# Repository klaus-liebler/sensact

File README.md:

# sensact

Verteilte Hausautomatisierung – Hardware, Firmware, Werkzeuge und Weboberfläche.

Stationen an einem gemeinsamen CAN-Bus lesen Taster und Drehgeber und schalten Licht, Rollläden, Pumpen
und Signale. Die kleinste Einheit ist die **App** (Taster, Lampe, Rollladen …) mit einer hausweit
eindeutigen Nummer; Apps schicken einander Kommandos, egal auf welcher Station sie laufen. Was wo
verdrahtet ist, beschreibt ein **XML-Hausmodell**, aus dem Konfiguration und Weboberfläche jeder Station
erzeugt werden.

**Dokumentation: [docs/README.md](docs/README.md)** – Fachkonzepte, Bedienung im Haus,
Weboberfläche, Betrieb und Änderungen.

## Inhalt des Repos

| Ordner | Inhalt |
|---|---|
| [`docs/`](docs/README.md) | Fachkonzepte und Nutzerdokumentation |
| [`firmware/sensact_firmware/`](firmware/sensact_firmware/README.md) | ESP32-S3-Basis-Firmware, Builder, Editor, Hausmodell (`model/`), Weboberfläche – mit Entwicklerdokumentation |
| [`firmware/sensact_firmware_f103/`](firmware/sensact_firmware_f103/README.md) | Firmware der sensactUp-Stationen (STM32F103) auf rtoos |
| [`espidf-components/sensact-applicationmodel/`](espidf-components/sensact-applicationmodel/README.md) | die Apps (gemeinsam für ESP32 und STM32F103) mit Host-Tests |
| `espidf-components/sensact-middleware/`, `sensact-hal/`, `sensactcommon/` | CAN-Codec, HAL-Basis, gemeinsame Typen |
| `firmware/sensact_firmware_stm32/`, `firmware/firmwareCubeIDE/` | Altfirmware der STM32F407-Station |
| `pcb/` | Platinen (KiCad) |
| `doc/` | Datenblätter |
| `runware/` | PC-Werkzeuge (UDP-Monitor) |

## Hardware

- **SensactHS** – Hutschienenmontage im Verteiler (Technikstationen mit I2C-Erweiterungen für Ein- und Ausgänge)
- **SensactUP** – Unterputzmontage im Raum (Taster, Drehgeber, Signal-LEDs)
- Spezialstationen für Fingerabdruckleser (Seitentür) und Außenbereich (Terrasse)

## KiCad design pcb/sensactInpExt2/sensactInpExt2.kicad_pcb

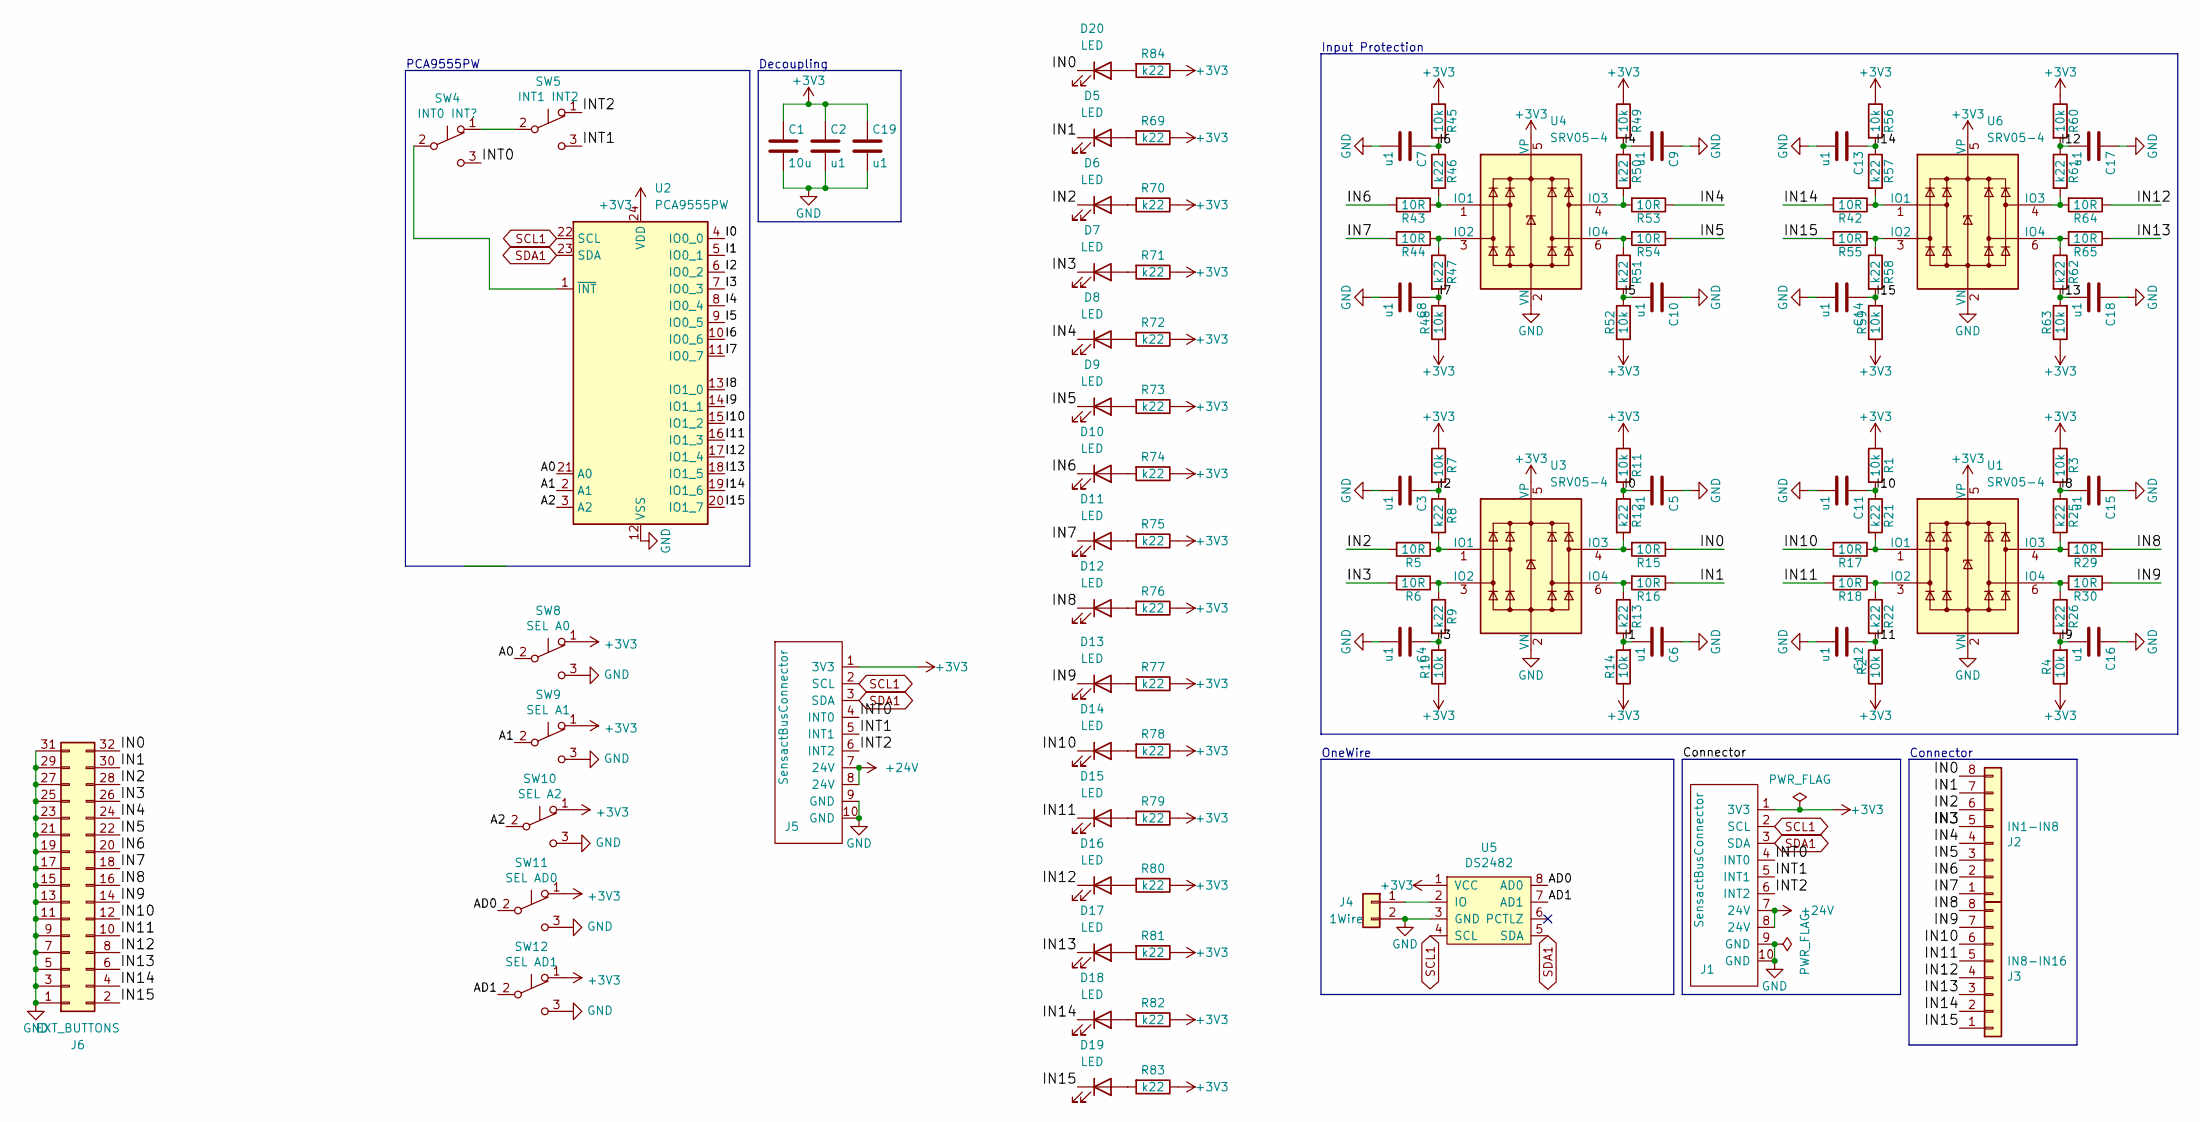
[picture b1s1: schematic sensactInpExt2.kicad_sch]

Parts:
C1: 10u; C_0805_2012Metric
C2, C3, C4, C5, C6, C7, C8, C9, C10, C11, C12, C13, C14, C15, C16, C17, C18, C19: u1; C_0402_1005Metric
D5, D6, D7, D8, D9, D10, D11, D12, D13, D14, D15, D16, D17, D18, D19, D20: LED; LED_1606
J1: SensactBusConnector; IDC-Header_2x05_P2.54mm_Horizontal
J2: IN1-IN8; PhoenixContact_MC_0,5_8-G-2.5_1x08_P2.50mm_Horizontal
J3: IN8-IN16; PhoenixContact_MC_0,5_8-G-2.5_1x08_P2.50mm_Horizontal
J4: 1Wire; PhoenixContact_MC_1,5_2-G-3.81_1x02_P3.81mm_Horizontal
J5: SensactBusConnector; PinSocket_2x06_P2.54mm_Vertical
J6: EXT_BUTTONS; PinHeader_2x16_P2.54mm_Horizontal
R1, R2, R3, R4, R7, R10, R11, R14, R45, R48, R49, R52, R56, R59, R60, R63: 10k; R_0402_1005Metric
R5, R6, R15, R16, R17, R18, R29, R30, R42, R43, R44, R53, R54, R55, R64, R65: 10R; R_0402_1005Metric
R8, R9, R12, R13, R21, R22, R25, R26, R46, R47, R50, R51, R57, R58, R61, R62, R69, R70, R71, R72, R73, R74, R75, R76, R77, R78, R79, R80, R81, R82, R83, R84: k22; R_0402_1005Metric
SW4: INT0 INT?; SW_SPDT_PCM12
SW5: INT1 INT2; SW_SPDT_PCM12
SW8: SEL A0; SW_SPDT_PCM12
SW9: SEL A1; SW_SPDT_PCM12
SW10: SEL A2; SW_SPDT_PCM12
SW11: SEL AD0; SW_SPDT_PCM12
SW12: SEL AD1; SW_SPDT_PCM12
U1, U3, U4, U6: SRV05-4; SOT-23-6
U2: PCA9555PW; TSSOP-24_4.4x7.8mm_P0.65mm
U5: DS2482; SOIC-8_3.9x4.9mm_P1.27mm

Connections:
+3V3: C1.1, C2.1, C19.1, J1.1 (3V3), J5.1 (3V3), R1.1, R2.1, R3.1, R4.1, R7.1, R10.1, R11.1, R14.1, R45.1, R48.1, R49.1, R52.1, R56.1, R59.1, R60.1, R63.1, R69.1, R70.1, R71.1, R72.1, R73.1, R74.1, R75.1, R76.1, R77.1, R78.1, R79.1, R80.1, R81.1, R82.1, R83.1, R84.1, SW8.1 (A), SW9.1 (A), SW10.1 (A), SW11.1 (A), SW12.1 (A), U1.5 (VP), U2.24 (VDD), U3.5 (VP), U4.5 (VP), U5.1 (VCC), U6.5 (VP)
+24V: J1.7 (24V), J1.8 (24V), J5.7 (24V), J5.8 (24V)
/A0: SW8.2 (B), U2.21 (A0)
/A1: SW9.2 (B), U2.2 (A1)
/A2: SW10.2 (B), U2.3 (A2)
/AD0: SW11.2 (B), U5.8 (AD0)
/AD1: SW12.2 (B), U5.7 (AD1)
/I0: C5.2, R11.2, R12.1, U2.4 (IO0_0)
/I1: C6.2, R13.2, R14.2, U2.5 (IO0_1)
/I2: C3.1, R7.2, R8.1, U2.6 (IO0_2)
/I3: C4.1, R9.2, R10.2, U2.7 (IO0_3)
/I4: C9.2, R49.2, R50.1, U2.8 (IO0_4)
/I5: C10.2, R51.2, R52.2, U2.9 (IO0_5)
/I6: C7.1, R45.2, R46.1, U2.10 (IO0_6)
/I7: C8.1, R47.2, R48.2, U2.11 (IO0_7)
/I8: C15.2, R3.2, R25.1, U2.13 (IO1_0)
/I9: C16.2, R4.2, R26.2, U2.14 (IO1_1)
/I10: C11.1, R1.2, R21.1, U2.15 (IO1_2)
/I11: C12.1, R2.2, R22.2, U2.16 (IO1_3)
/I12: C17.2, R60.2, R61.1, U2.17 (IO1_4)
/I13: C18.2, R62.2, R63.2, U2.18 (IO1_5)
/I14: C13.1, R56.2, R57.1, U2.19 (IO1_6)
/I15: C14.1, R58.2, R59.2, U2.20 (IO1_7)
/IN0: D20.1 (K), J2.8, J6.32, R15.1
/IN1: D5.1 (K), J2.7, J6.30, R16.1
/IN2: D6.1 (K), J2.6, J6.28, R5.2
/IN3: D7.1 (K), J2.5, J6.26, R6.2
/IN4: D8.1 (K), J2.4, J6.24, R53.1
/IN5: D9.1 (K), J2.3, J6.22, R54.1
/IN6: D10.1 (K), J2.2, J6.20, R43.2
/IN7: D11.1 (K), J2.1, J6.18, R44.2
/IN8: D12.1 (K), J3.8, J6.16, R29.1
/IN9: D13.1 (K), J3.7, J6.14, R30.1
/IN10: D14.1 (K), J3.6, J6.12, R17.2
/IN11: D15.1 (K), J3.5, J6.10, R18.2
/IN12: D16.1 (K), J3.4, J6.8, R64.1
/IN13: D17.1 (K), J3.3, J6.6, R65.1
/IN14: D18.1 (K), J3.2, J6.4, R42.2
/IN15: D19.1 (K), J3.1, J6.2, R55.2
/INT0: J1.4 (INT0), J5.4 (INT0), SW4.3 (C)
/INT1: J1.5 (INT1), J5.5 (INT1), SW5.3 (C)
/INT2: J1.6 (INT2), J5.6 (INT2), SW5.1 (A)
GND: C1.2, C2.2, C3.2, C4.2, C5.1, C6.1, C7.2, C8.2, C9.1, C10.1, C11.2, C12.2, C13.2, C14.2, C15.1, C16.1, C17.1, C18.1, C19.2, J1.9 (GND), J1.10 (GND), J4.2, J5.9 (GND), J5.10 (GND), J6.1, J6.3, J6.5, J6.7, J6.9, J6.11, J6.13, J6.15, J6.17, J6.19, J6.21, J6.23, J6.25, J6.27, J6.29, J6.31, SW8.3 (C), SW9.3 (C), SW10.3 (C), SW11.3 (C), SW12.3 (C), U1.2 (VN), U2.12 (VSS), U3.2 (VN), U4.2 (VN), U5.3 (GND), U6.2 (VN)
unnamed: D5.2 (A), R69.2
unnamed: D6.2 (A), R70.2
unnamed: D7.2 (A), R71.2
unnamed: D8.2 (A), R72.2
unnamed: D9.2 (A), R73.2
unnamed: D10.2 (A), R74.2
unnamed: D11.2 (A), R75.2
unnamed: D12.2 (A), R76.2
unnamed: D13.2 (A), R77.2
unnamed: D14.2 (A), R78.2
unnamed: D15.2 (A), R79.2
unnamed: D16.2 (A), R80.2
unnamed: D17.2 (A), R81.2
unnamed: D18.2 (A), R82.2
unnamed: D19.2 (A), R83.2
unnamed: D20.2 (A), R84.2
unnamed: J4.1, U5.2 (IO)
unnamed: SW4.1 (A), SW5.2 (B)
unnamed: SW4.2 (B), U2.1 (~INT)
unnamed: R17.1, R21.2, U1.1 (IO1)
unnamed: R18.1, R22.1, U1.3 (IO2)
unnamed: R25.2, R29.2, U1.4 (IO3)
unnamed: R26.1, R30.2, U1.6 (IO4)
unnamed: R5.1, R8.2, U3.1 (IO1)
unnamed: R6.1, R9.1, U3.3 (IO2)
unnamed: R12.2, R15.2, U3.4 (IO3)
unnamed: R13.1, R16.2, U3.6 (IO4)
unnamed: R43.1, R46.2, U4.1 (IO1)
unnamed: R44.1, R47.1, U4.3 (IO2)
unnamed: R50.2, R53.2, U4.4 (IO3)
unnamed: R51.1, R54.2, U4.6 (IO4)
unnamed: R42.1, R57.2, U6.1 (IO1)
unnamed: R55.1, R58.1, U6.3 (IO2)
unnamed: R61.2, R64.2, U6.4 (IO3)
unnamed: R62.1, R65.2, U6.6 (IO4)
SCL1: J1.2 (SCL), J5.2 (SCL), U2.22 (SCL), U5.4 (SCL)
SDA1: J1.3 (SDA), J5.3 (SDA), U2.23 (SDA), U5.5 (SDA)

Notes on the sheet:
OneWire
Decoupling
Input Protection
Connector
PCA9555PW

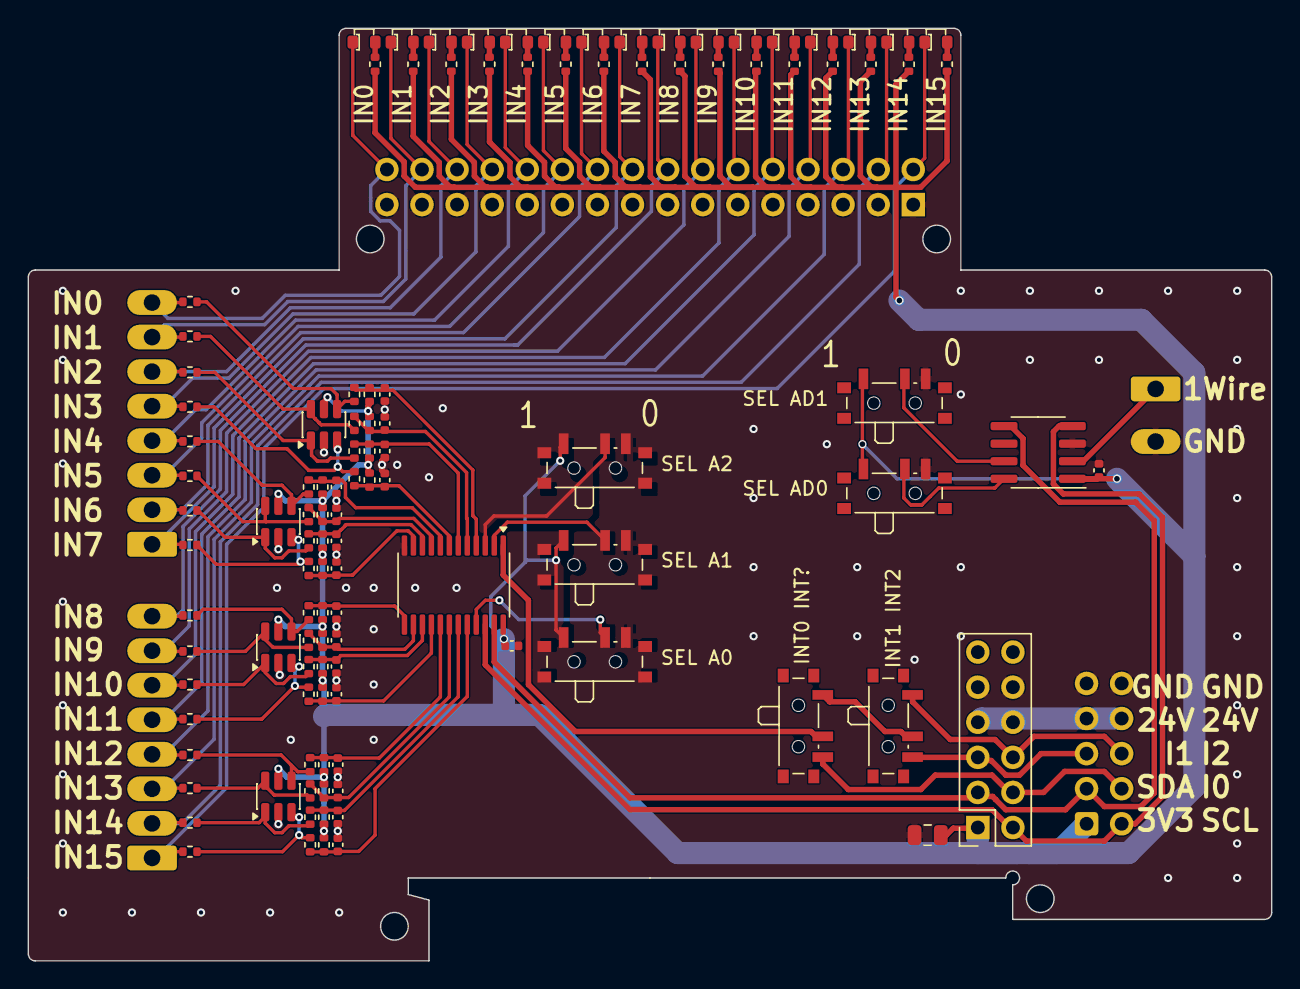
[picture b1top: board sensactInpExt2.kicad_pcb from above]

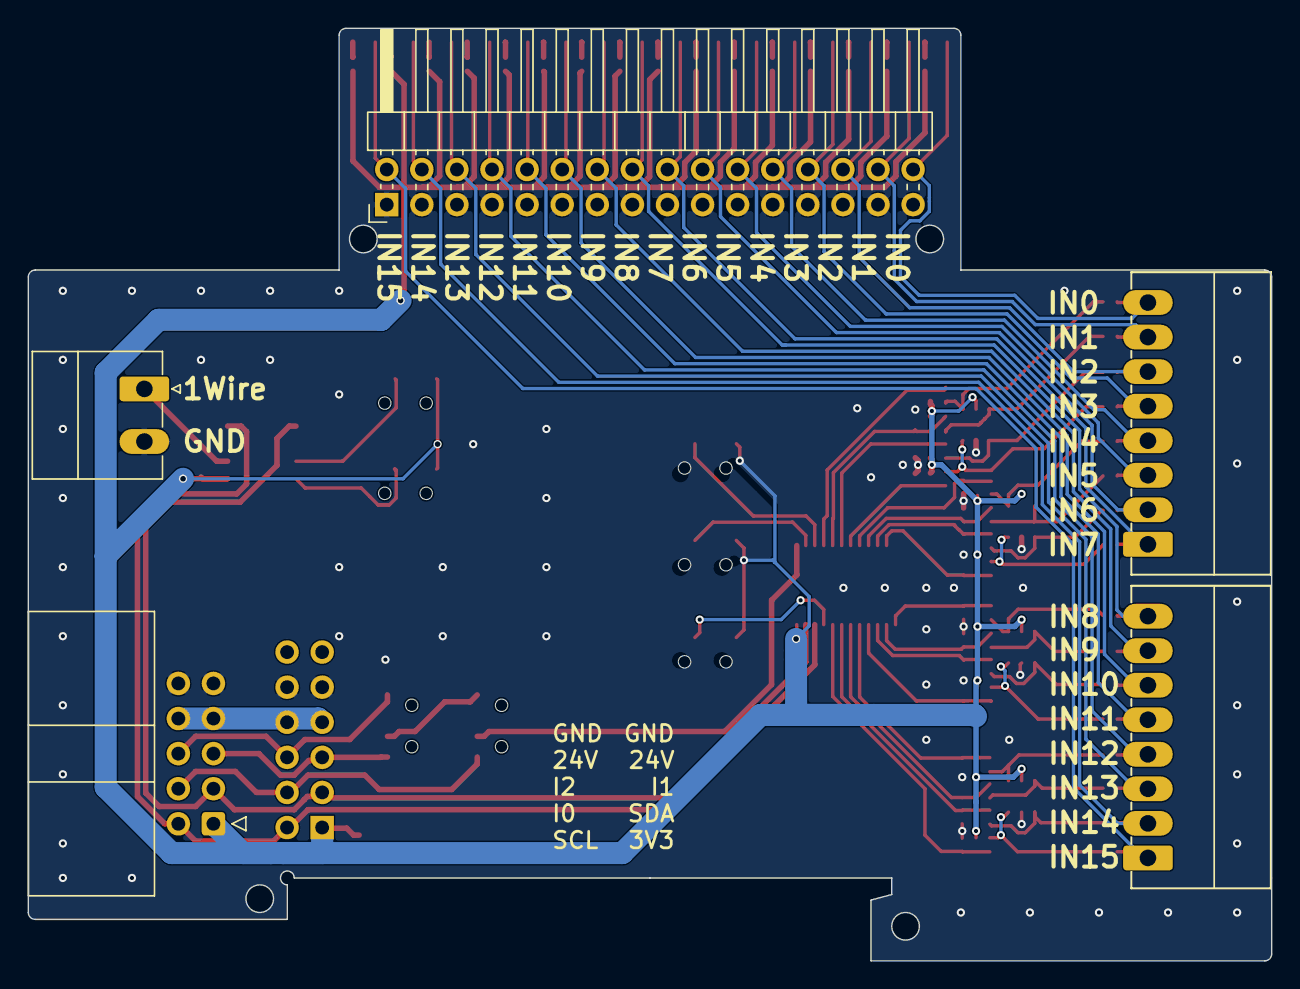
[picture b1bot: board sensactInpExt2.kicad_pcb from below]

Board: 2 copper layers, 90.0 x 67.5 mm, 118 parts (5 on the bottom side), 80 nets.

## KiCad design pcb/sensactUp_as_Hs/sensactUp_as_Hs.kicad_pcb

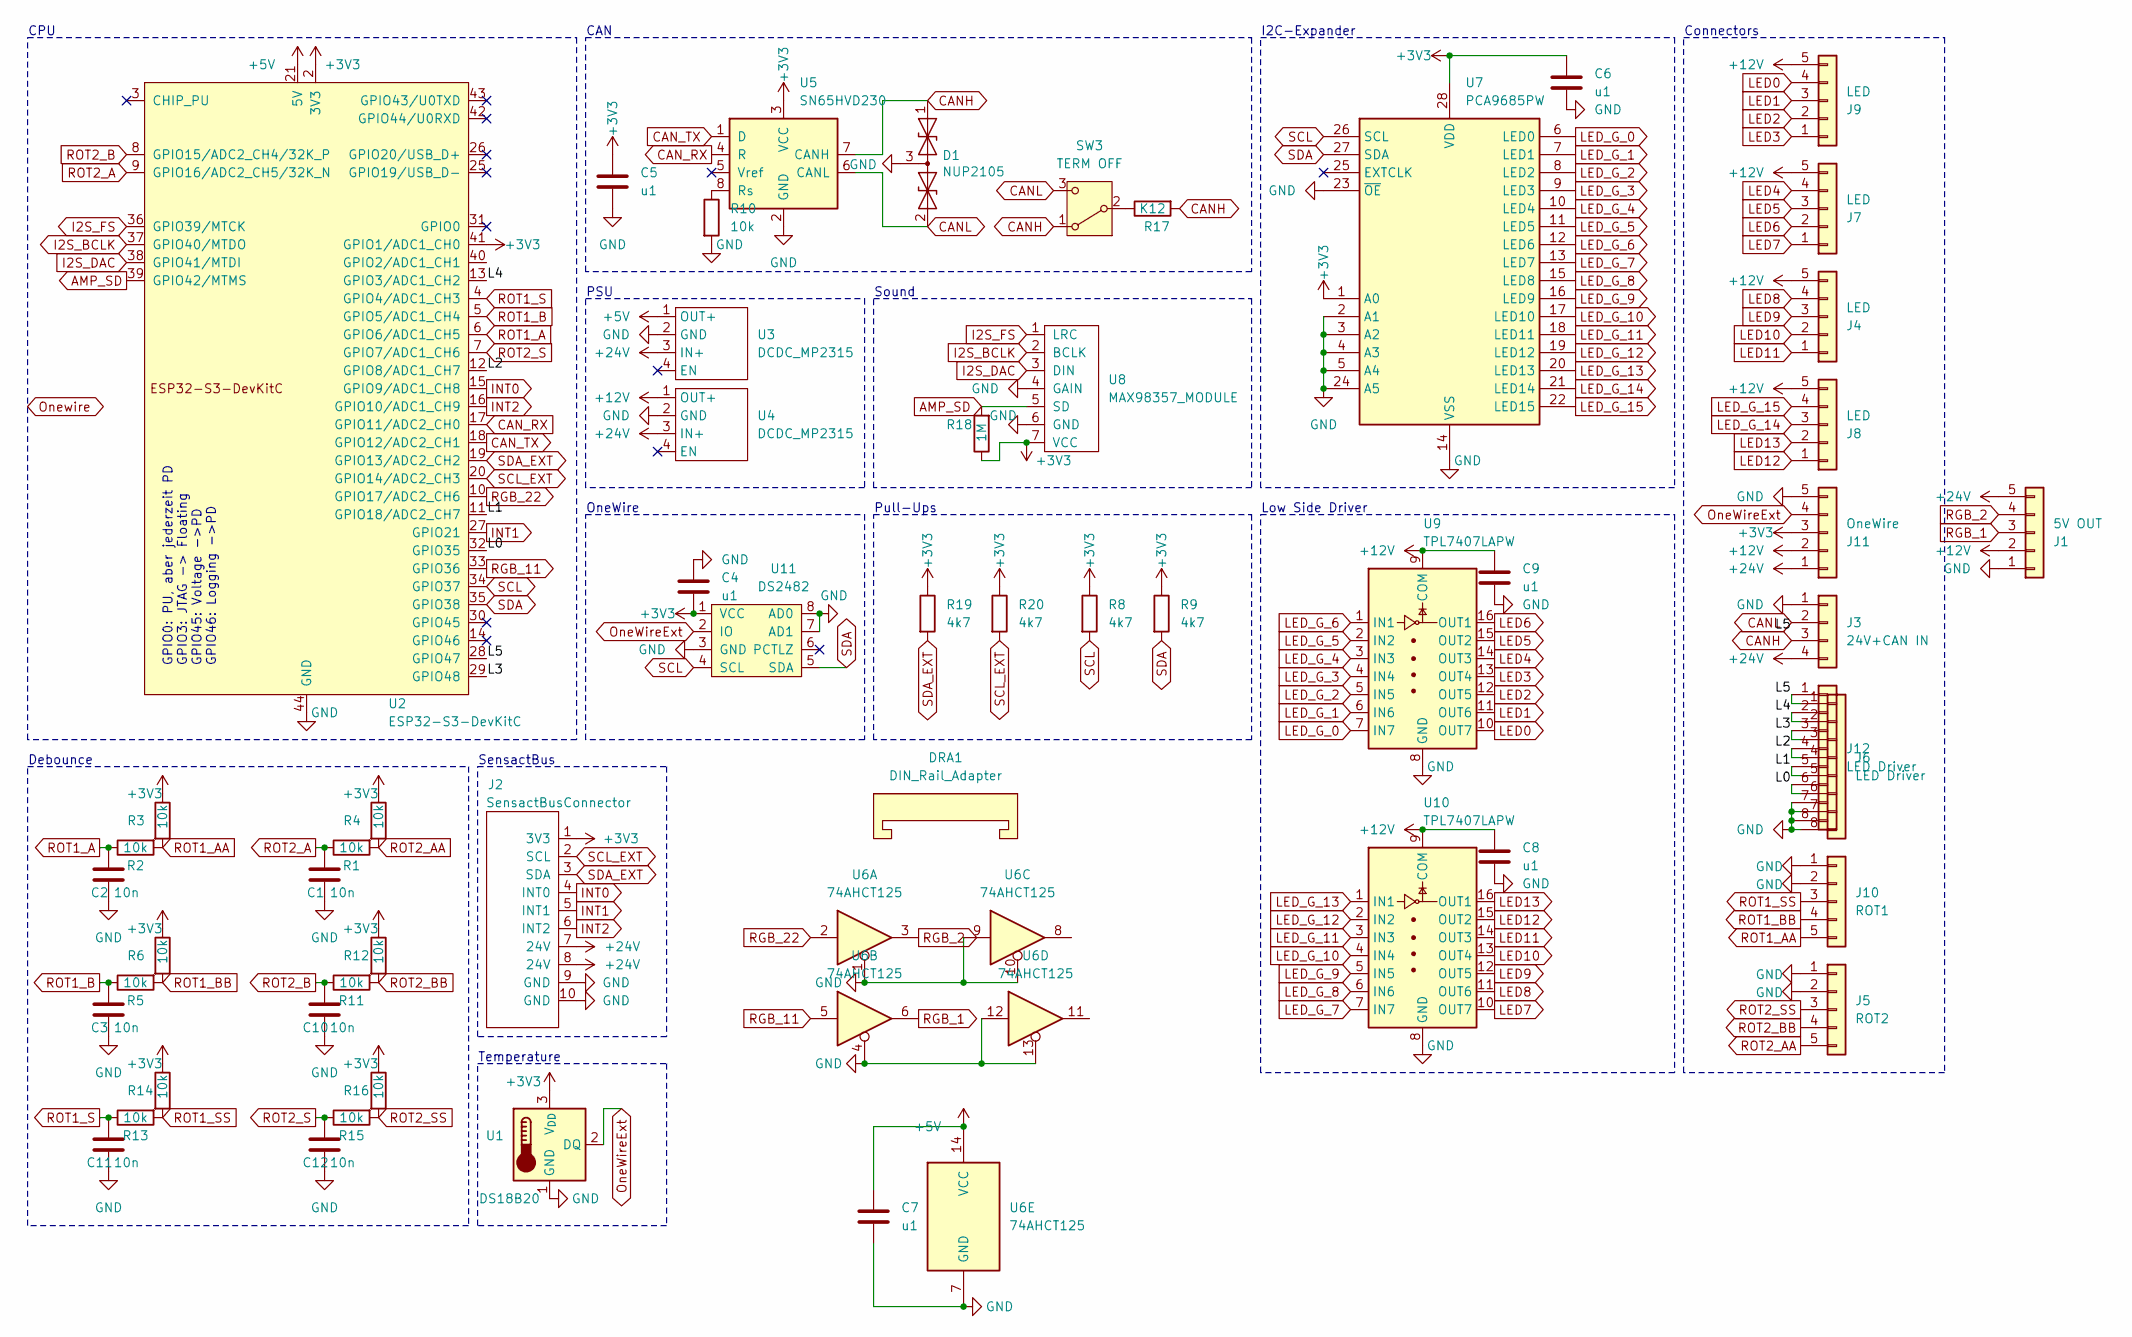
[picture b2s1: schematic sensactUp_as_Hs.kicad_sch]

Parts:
C1, C2, C3, C10, C11, C12: 10n; C_0805_2012Metric_Pad1.18x1.45mm_HandSolder
C4, C5, C6, C7, C8, C9: u1; C_0805_2012Metric_Pad1.18x1.45mm_HandSolder
D1: NUP2105; SOT-23_Handsoldering; MPN NUP2105L
DRA1: DIN_Rail_Adapter; Camdenboss CNMB-6
J1: 5V OUT; PhoenixContact_MCV_1,5_5-G-3.81_1x05_P3.81mm_Vertical_small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
J2: SensactBusConnector; IDC-Header_2x05_P2.54mm_Horizontal
J3: 24V+CAN IN; PhoenixContact_MCV_1,5_4-G-3.5_1x04_P3.50mm_Vertical_smalle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
J4, J7, J8, J9: LED; PhoenixContact_MCV_1,5_5-G-3.81_1x05_P3.81mm_Vertical_small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
J5: ROT2; PhoenixContact_MCV_1,5_5-G-3.81_1x05_P3.81mm_Vertical_small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
J6: LED Driver; PhoenixContact_MC_0,5_8-G-2.5_1x08_P2.50mm_Horizontal
J10: ROT1; PhoenixContact_MCV_1,5_5-G-3.81_1x05_P3.81mm_Vertical_small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
J11: OneWire; PhoenixContact_MCV_1,5_5-G-3.81_1x05_P3.81mm_Vertical_small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
J12: LED Driver; PinHeader_1x08_P2.54mm_Vertical
R1, R2, R3, R4, R5, R6, R10, R11, R12, R13, R14, R15, R16: 10k; R_0805_2012Metric_Pad1.20x1.40mm_HandSolder
R8, R9, R19, R20: 4k7; R_0805_2012Metric_Pad1.20x1.40mm_HandSolder
R17: K12; R_1206_3216Metric_Pad1.30x1.75mm_HandSolder; MPN 1206W4F1200T5E
R18: 1M; R_0805_2012Metric_Pad1.20x1.40mm_HandSolder
SW3: TERM OFF; Switch_SS12D00
U1: DS18B20; TO-92L_HandSolder
U2: ESP32-S3-DevKitC; ESP32-S3 chinese dev board
U3, U4: DCDC_MP2315; DCDC_MP2315_horizontal
U5: SN65HVD230; SOIC-8_3.9x4.9mm_P1.27mm
U6: 74AHCT125; SOIC-14_3.9x8.7mm_P1.27mm_handsolder
U7: PCA9685PW; TSSOP-28_4.4x9.7mm_Pitch0.65mm_handsolder
U8: MAX98357_MODULE; PinHeader_1x07_P2.54mm_Vertical
U9, U10: TPL7407LAPW; TSSOP-16_4.4x5mm_P0.65mm
U11: DS2482; SOIC-8_3.9x4.9mm_P1.27mm_handsolder

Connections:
+3V3: C4.1, C5.1, C6.1, J2.1 (3V3), J11.3, R3.1, R4.1, R6.1, R8.1, R9.1, R12.1, R14.1, R16.1, R18.1, R19.1, R20.1, U1.3 (V_{DD}), U2.1 (3V3), U2.2 (3V3), U2.41 (GPIO1/ADC1_CH0), U5.3 (VCC), U7.1 (A0), U7.28 (VDD), U8.7 (VCC), U11.1 (VCC)
+5V: C7.2, U2.21 (5V), U3.1 (OUT+), U6.14 (VCC)
+12V: C8.1, C9.1, J1.2, J4.5, J7.5, J8.5, J9.5, J11.2, U4.1 (OUT+), U9.9 (COM), U10.9 (COM)
+24V: J1.5, J2.7 (24V), J2.8 (24V), J3.4, J11.1, U3.3 (IN+), U4.3 (IN+)
/L0: J6.6, J12.6, U2.32 (GPIO35)
/L1: J6.5, J12.5, U2.11 (GPIO18/ADC2_CH7)
/L2: J6.4, J12.4, U2.12 (GPIO8/ADC1_CH7)
/L3: J6.3, J12.3, U2.29 (GPIO48)
/L4: J6.2, J12.2, U2.13 (GPIO3/ADC1_CH2)
/L5: J6.1, J12.1, U2.28 (GPIO47)
AMP_SD: R18.2, U2.39 (GPIO42/MTMS), U8.5 (SD)
CANH: D1.1 (A1), J3.3, R17.2, SW3.1 (A), U5.7 (CANH)
CANL: D1.2 (A2), J3.2, SW3.3 (C), U5.6 (CANL)
CAN_RX: U2.17 (GPIO11/ADC2_CH0), U5.4 (R)
CAN_TX: U2.18 (GPIO12/ADC2_CH1), U5.1 (D)
GND: C1.1, C2.1, C3.1, C4.2, C5.2, C6.2, C7.1, C8.2, C9.2, C10.1, C11.1, C12.1, D1.3 (common), J1.1, J2.9 (GND), J2.10 (GND), J3.1, J5.1, J5.2, J6.7, J6.8, J10.1, J10.2, J11.5, J12.7, J12.8, R10.2, U1.1 (GND), U2.22 (GND), U2.23 (GND), U2.24 (GND), U2.44 (GND), U3.2 (GND), U4.2 (GND), U5.2 (GND), U6.1, U6.4, U6.7 (GND), U6.9, U6.10, U6.12, U6.13, U7.2 (A1), U7.3 (A2), U7.4 (A3), U7.5 (A4), U7.14 (VSS), U7.23 (~OE), U7.24 (A5), U8.4 (GAIN), U8.6 (GND), U9.8 (GND), U10.8 (GND), U11.3 (GND), U11.7 (AD1), U11.8 (AD0)
I2S_BCLK: U2.37 (GPIO40/MTDO), U8.2 (BCLK)
I2S_DAC: U2.38 (GPIO41/MTDI), U8.3 (DIN)
I2S_FS: U2.36 (GPIO39/MTCK), U8.1 (LRC)
INT0: J2.4 (INT0), U2.15 (GPIO9/ADC1_CH8)
INT1: J2.5 (INT1), U2.27 (GPIO21)
INT2: J2.6 (INT2), U2.16 (GPIO10/ADC1_CH9)
LED0: J9.4, U9.10 (OUT7)
LED1: J9.3, U9.11 (OUT6)
LED2: J9.2, U9.12 (OUT5)
LED3: J9.1, U9.13 (OUT4)
LED4: J7.4, U9.14 (OUT3)
LED5: J7.3, U9.15 (OUT2)
LED6: J7.2, U9.16 (OUT1)
LED7: J7.1, U10.10 (OUT7)
LED8: J4.4, U10.11 (OUT6)
LED9: J4.3, U10.12 (OUT5)
LED10: J4.2, U10.13 (OUT4)
LED11: J4.1, U10.14 (OUT3)
LED12: J8.1, U10.15 (OUT2)
LED13: J8.2, U10.16 (OUT1)
LED_G_0: U7.6 (LED0), U9.7 (IN7)
LED_G_1: U7.7 (LED1), U9.6 (IN6)
LED_G_2: U7.8 (LED2), U9.5 (IN5)
LED_G_3: U7.9 (LED3), U9.4 (IN4)
LED_G_4: U7.10 (LED4), U9.3 (IN3)
LED_G_5: U7.11 (LED5), U9.2 (IN2)
LED_G_6: U7.12 (LED6), U9.1 (IN1)
LED_G_7: U7.13 (LED7), U10.7 (IN7)
LED_G_8: U7.15 (LED8), U10.6 (IN6)
LED_G_9: U7.16 (LED9), U10.5 (IN5)
LED_G_10: U7.17 (LED10), U10.4 (IN4)
LED_G_11: U7.18 (LED11), U10.3 (IN3)
LED_G_12: U7.19 (LED12), U10.2 (IN2)
LED_G_13: U7.20 (LED13), U10.1 (IN1)
LED_G_14: J8.3, U7.21 (LED14)
LED_G_15: J8.4, U7.22 (LED15)
unnamed: R17.1, SW3.2 (B)
unnamed: R10.1, U5.8 (Rs)
OneWireExt: J11.4, U1.2 (DQ), U11.2 (IO)
RGB_1: J1.3, U6.6
RGB_2: J1.4, U6.3
RGB_11: U2.33 (GPIO36), U6.5
RGB_22: U2.10 (GPIO17/ADC2_CH6), U6.2
ROT1_A: C2.2, R2.1, U2.6 (GPIO6/ADC1_CH5)
ROT1_AA: J10.5, R2.2, R3.2
ROT1_B: C3.2, R5.1, U2.5 (GPIO5/ADC1_CH4)
ROT1_BB: J10.4, R5.2, R6.2
ROT1_S: C11.2, R13.1, U2.4 (GPIO4/ADC1_CH3)
ROT1_SS: J10.3, R13.2, R14.2
ROT2_A: C1.2, R1.1, U2.9 (GPIO16/ADC2_CH5/32K_N)
ROT2_AA: J5.5, R1.2, R4.2
ROT2_B: C10.2, R11.1, U2.8 (GPIO15/ADC2_CH4/32K_P)
ROT2_BB: J5.4, R11.2, R12.2
ROT2_S: C12.2, R15.1, U2.7 (GPIO7/ADC1_CH6)
ROT2_SS: J5.3, R15.2, R16.2
SCL: R8.2, U2.34 (GPIO37), U7.26 (SCL), U11.4 (SCL)
SCL_EXT: J2.2 (SCL), R20.2, U2.20 (GPIO14/ADC2_CH3)
SDA: R9.2, U2.35 (GPIO38), U7.27 (SDA), U11.5 (SDA)
SDA_EXT: J2.3 (SDA), R19.2, U2.19 (GPIO13/ADC2_CH2)

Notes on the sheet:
GPIO0: PU, aber jederzeit PD GPIO3: JTAG -> Floating GPIO45: Voltage ->PD GPIO46: Logging ->PD
Low Side Driver
OneWire
Sound
CAN
Pull-Ups
I2C-Expander
Debounce
SensactBus
CPU
PSU
Connectors
Temperature

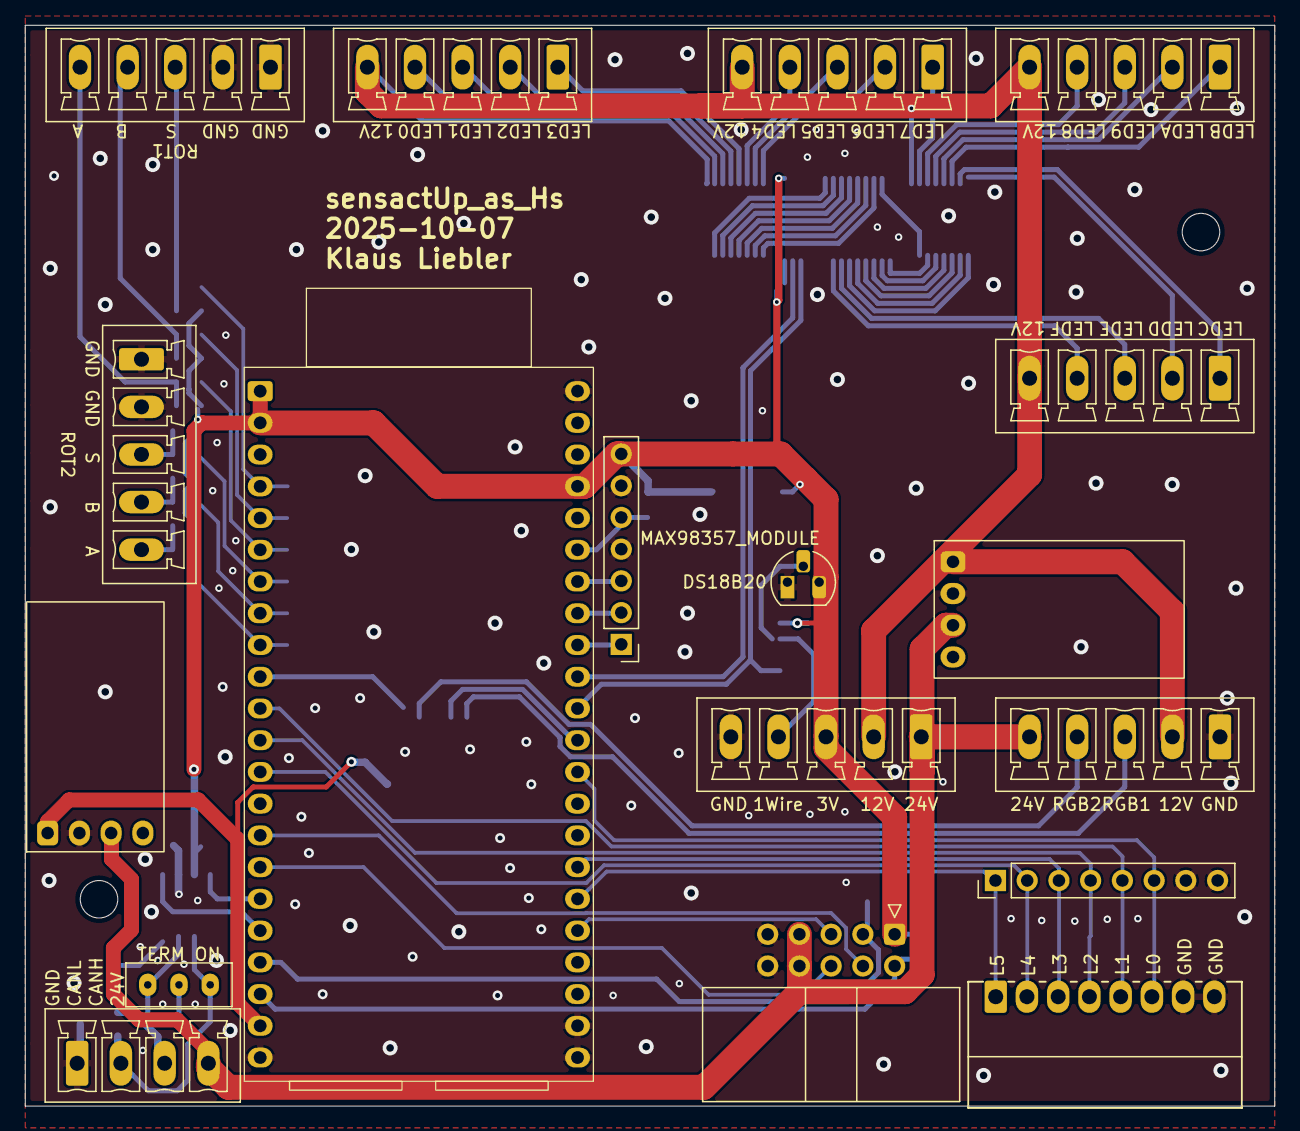
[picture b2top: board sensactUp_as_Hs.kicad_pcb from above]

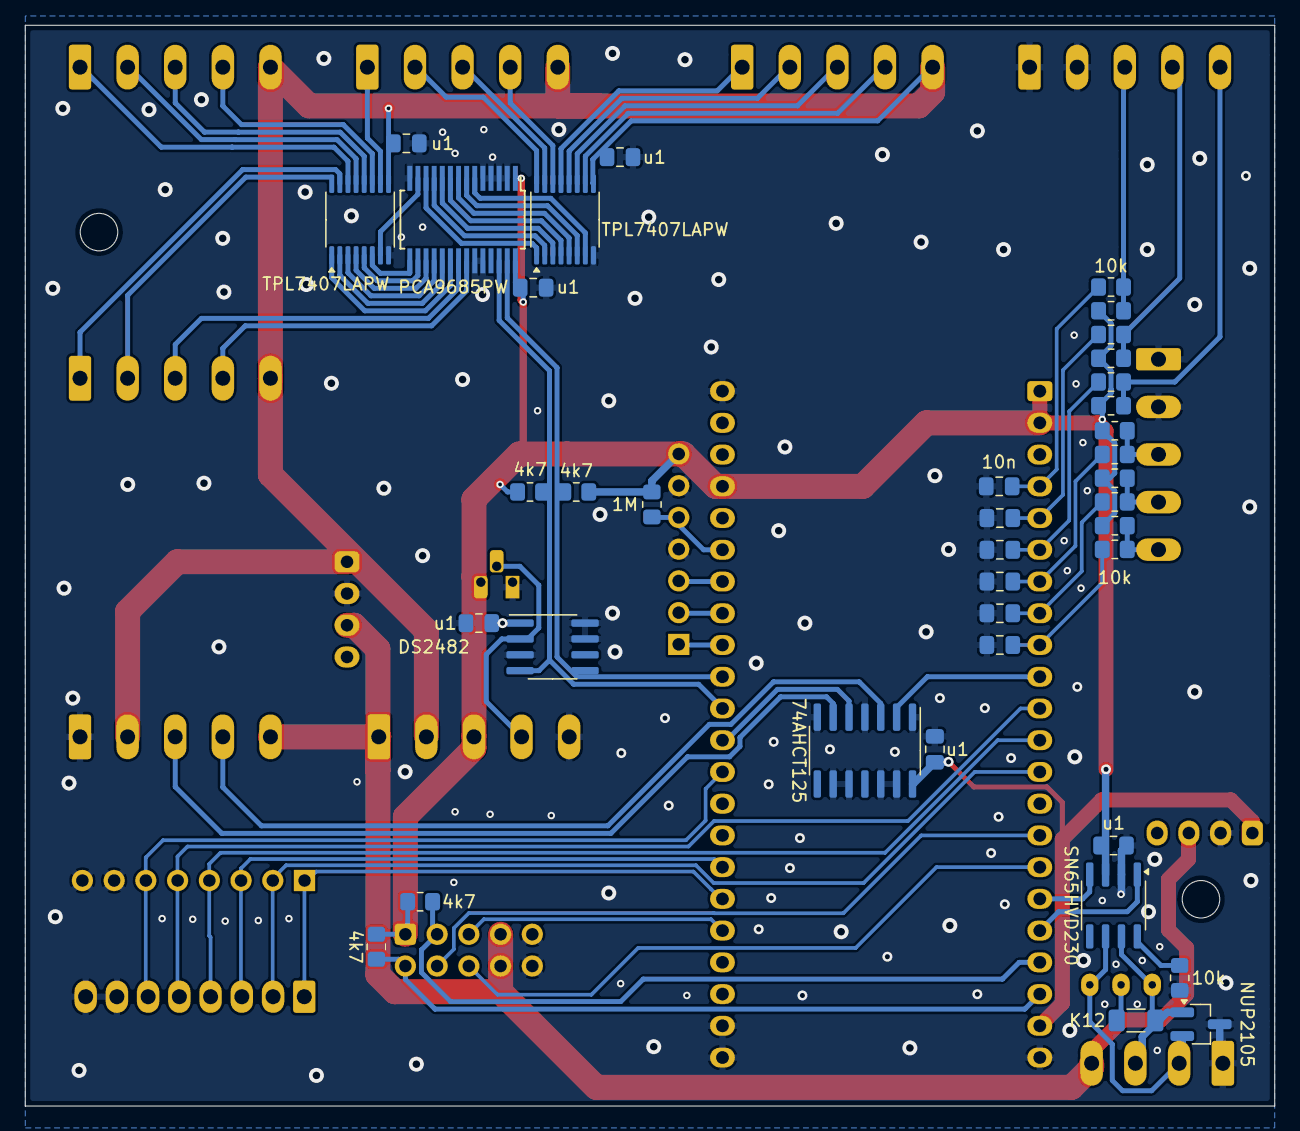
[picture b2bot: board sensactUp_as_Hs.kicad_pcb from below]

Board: 2 copper layers, 100.0 x 86.5 mm, 57 parts (38 on the bottom side), 75 nets.

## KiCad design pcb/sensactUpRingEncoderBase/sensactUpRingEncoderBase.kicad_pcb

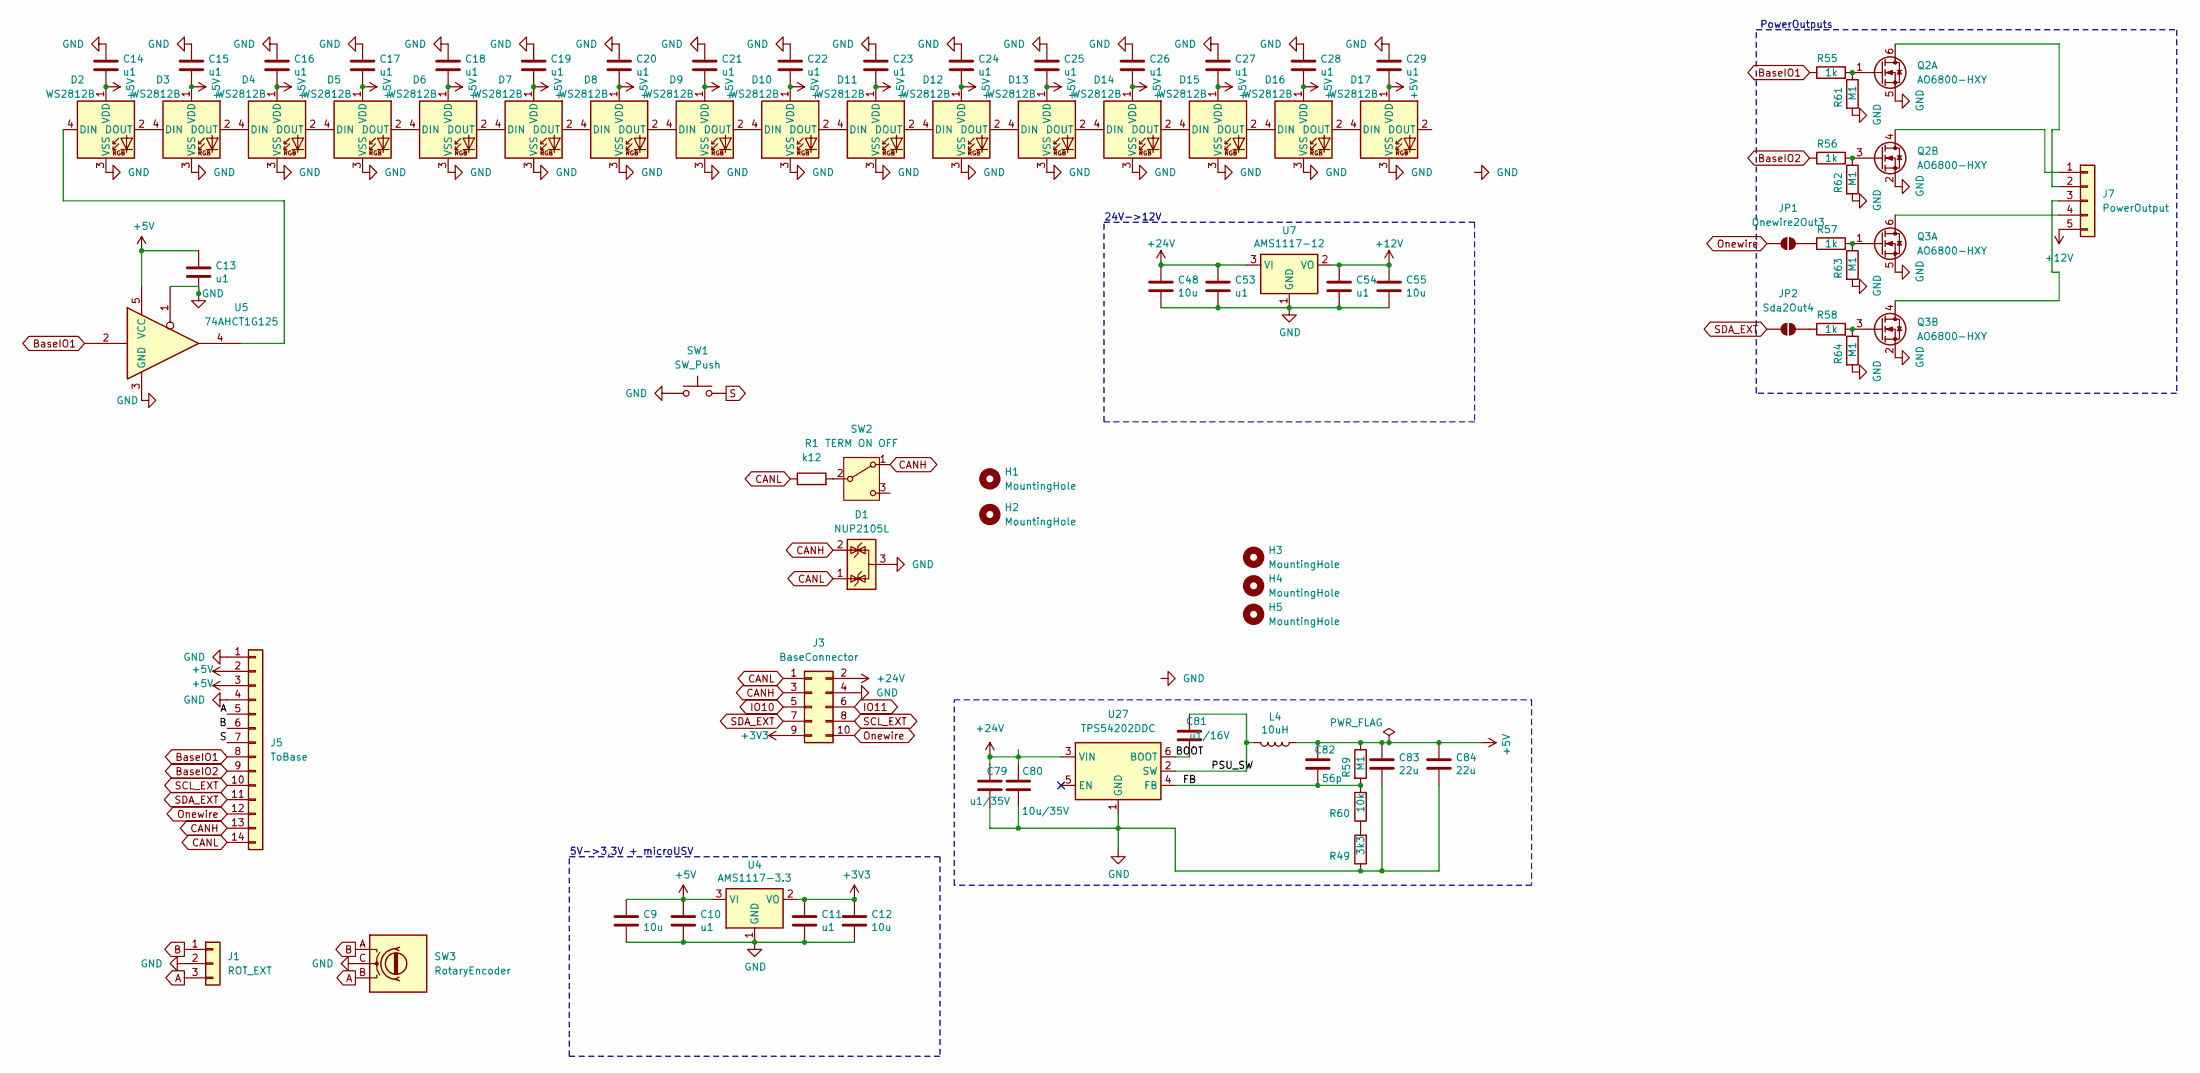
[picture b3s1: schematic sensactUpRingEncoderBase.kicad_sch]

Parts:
C9, C12, C48, C55: 10u; C_0805_2012Metric_Pad1.18x1.45mm_HandSolder
C10, C11, C13, C14, C15, C16, C17, C18, C19, C20, C21, C22, C23, C24, C25, C26, C27, C28, C29, C53, C54: u1; C_0805_2012Metric_Pad1.18x1.45mm_HandSolder
C79: u1/35V; R_0805_2012Metric_Pad1.20x1.40mm_HandSolder; MPN CC0603KRX7R9BB104
C80: 10u/35V; C_1206_3216Metric_Pad1.33x1.80mm_HandSolder; MPN CGA0805X5R106K350MT
C81: u1/16V; R_0805_2012Metric_Pad1.20x1.40mm_HandSolder; MPN CC0603KRX7R9BB104
C82: 56p; R_0805_2012Metric_Pad1.20x1.40mm_HandSolder; MPN CC0402JRNPO9BN560
C83, C84: 22u; R_0805_2012Metric_Pad1.20x1.40mm_HandSolder; MPN CL10A226MP8NUNE
D1: NUP2105L; SOT-23_Handsoldering
D2, D3, D4, D5, D6, D7, D8, D9, D10, D11, D12, D13, D14, D15, D16, D17: WS2812B; LED_WS2812B-Mini_PLCC4_3.5x3.5mm
H1, H2: MountingHole; MountingHole_5mm
H3, H4, H5: MountingHole; MountingHole_2.2mm_M2
J1: ROT_EXT; PhoenixContact_MCV_1,5_3-G-3.5_1x03_P3.50mm_Vertical_smalle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
J3: BaseConnector; IDC-Header_2x05_P2.54mm_Vertical
J5: ToBase; Hirose_FH12-14S-0.5SH_1x14-1MP_P0.50mm_Horizontal_handsolder
J7: PowerOutput; PinHeader_1x05_P2.54mm_Vertical
JP1: Onewire2Out3; SolderJumper-2_P1.3mm_Open_RoundedPad1.0x1.5mm
JP2: Sda2Out4; SolderJumper-2_P1.3mm_Open_RoundedPad1.0x1.5mm
L4: 10uH; L_0630; MPN FXL0630-100-M
Q2, Q3: AO6800-HXY; SOT-23-6_Handsoldering
R1: k12; R_0805_2012Metric_Pad1.20x1.40mm_HandSolder
R49: 3k3; R_0805_2012Metric_Pad1.20x1.40mm_HandSolder; MPN 0402WGF3301TCE
R55, R56, R57, R58: 1k; R_0805_2012Metric_Pad1.20x1.40mm_HandSolder
R59, R61, R62, R63, R64: M1; R_0805_2012Metric_Pad1.20x1.40mm_HandSolder; MPN 0201WMF1003TEE
R60: 10k; R_0805_2012Metric_Pad1.20x1.40mm_HandSolder; MPN 0201WMF1002TEE
SW1: SW_Push; Button_12mm_ANCHOR_CENTER
SW2: TERM ON OFF; SW_SPDT_PCM12_handsolder
SW3: RotaryEncoder; Encoder Alps-Alpine EC35
U4: AMS1117-3.3; SOT-223-3_TabPin2_HANDSOLDER
U5: 74AHCT1G125; SOT-353_SC-70-5_Handsoldering
U7: AMS1117-12; SOT-223-3_TabPin2_HANDSOLDER
U27: TPS54202DDC; SOT-23-6_Handsoldering; MPN TPS54202DDCR

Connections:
+3V3: C11.1, C12.1, J3.9, U4.2 (VO)
+5V: C9.1, C10.1, C13.1, C14.2, C15.2, C16.2, C17.2, C18.2, C19.2, C20.2, C21.2, C22.2, C23.2, C24.2, C25.2, C26.2, C27.2, C28.2, C29.2, C82.2, C83.1, C84.1, D2.1 (VDD), D3.1 (VDD), D4.1 (VDD), D5.1 (VDD), D6.1 (VDD), D7.1 (VDD), D8.1 (VDD), D9.1 (VDD), D10.1 (VDD), D11.1 (VDD), D12.1 (VDD), D13.1 (VDD), D14.1 (VDD), D15.1 (VDD), D16.1 (VDD), D17.1 (VDD), J5.2, J5.3, L4.1, R59.1, U4.3 (VI), U5.5 (VCC)
+12V: C54.1, C55.1, J7.5, U7.2 (VO)
+24V: C48.1, C53.1, C79.2, C80.2, J3.2, U7.3 (VI), U27.3 (VIN)
/BOOT: C81.1, U27.6 (BOOT)
/FB: C82.1, R59.2, R60.2, U27.4 (FB)
/PSU_SW: C81.2, L4.2, U27.2 (SW)
A: J1.3, J5.5, SW3.B
B: J1.1, J5.6, SW3.A
BaseIO1: J5.8, R55.1, U5.2
BaseIO2: J5.9, R56.1
CANH: D1.2 (K), J3.3, J5.13, SW2.1 (A)
CANL: D1.1 (K), J3.1, J5.14, R1.1
GND: C9.2, C10.2, C11.2, C12.2, C13.2, C14.1, C15.1, C16.1, C17.1, C18.1, C19.1, C20.1, C21.1, C22.1, C23.1, C24.1, C25.1, C26.1, C27.1, C28.1, C29.1, C48.2, C53.2, C54.2, C55.2, C79.1, C80.1, C83.2, C84.2, D1.3 (A), D2.3 (VSS), D3.3 (VSS), D4.3 (VSS), D5.3 (VSS), D6.3 (VSS), D7.3 (VSS), D8.3 (VSS), D9.3 (VSS), D10.3 (VSS), D11.3 (VSS), D12.3 (VSS), D13.3 (VSS), D14.3 (VSS), D15.3 (VSS), D16.3 (VSS), D17.3 (VSS), J1.2, J3.4, J5.1, J5.4, Q2.2 (S), Q2.5 (S), Q3.2 (S), Q3.5 (S), R49.1, R61.2, R62.2, R63.2, R64.2, SW1.1, SW3.C, U4.1 (GND), U5.1, U5.3 (GND), U7.1 (GND), U27.1 (GND)
IO10: J3.5
IO11: J3.6
unnamed: D2.4 (DIN), U5.4
unnamed: D2.2 (DOUT), D3.4 (DIN)
unnamed: D3.2 (DOUT), D4.4 (DIN)
unnamed: D4.2 (DOUT), D5.4 (DIN)
unnamed: D5.2 (DOUT), D6.4 (DIN)
unnamed: D6.2 (DOUT), D7.4 (DIN)
unnamed: D7.2 (DOUT), D8.4 (DIN)
unnamed: D8.2 (DOUT), D9.4 (DIN)
unnamed: D9.2 (DOUT), D10.4 (DIN)
unnamed: D10.2 (DOUT), D11.4 (DIN)
unnamed: D11.2 (DOUT), D12.4 (DIN)
unnamed: D12.2 (DOUT), D13.4 (DIN)
unnamed: D13.2 (DOUT), D14.4 (DIN)
unnamed: D14.2 (DOUT), D15.4 (DIN)
unnamed: D15.2 (DOUT), D16.4 (DIN)
unnamed: D16.2 (DOUT), D17.4 (DIN)
unnamed: J7.1, Q2.4 (D)
unnamed: J7.2, Q2.6 (D)
unnamed: J7.3, Q3.4 (D)
unnamed: J7.4, Q3.6 (D)
unnamed: JP1.2 (B), R57.1
unnamed: JP2.2 (B), R58.1
unnamed: Q2.1 (G), R55.2, R61.1
unnamed: Q2.3 (G), R56.2, R62.1
unnamed: Q3.1 (G), R57.2, R63.1
unnamed: Q3.3 (G), R58.2, R64.1
unnamed: R49.2, R60.1
unnamed: R1.2, SW2.2 (B)
Onewire: J3.10, J5.12, JP1.1 (A)
S: J5.7, SW1.2
SCL_EXT: J3.8, J5.10
SDA_EXT: J3.7, J5.11, JP2.1 (A)

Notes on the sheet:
PowerOutputs
5V->3,3V + microUSV
24V->12V
